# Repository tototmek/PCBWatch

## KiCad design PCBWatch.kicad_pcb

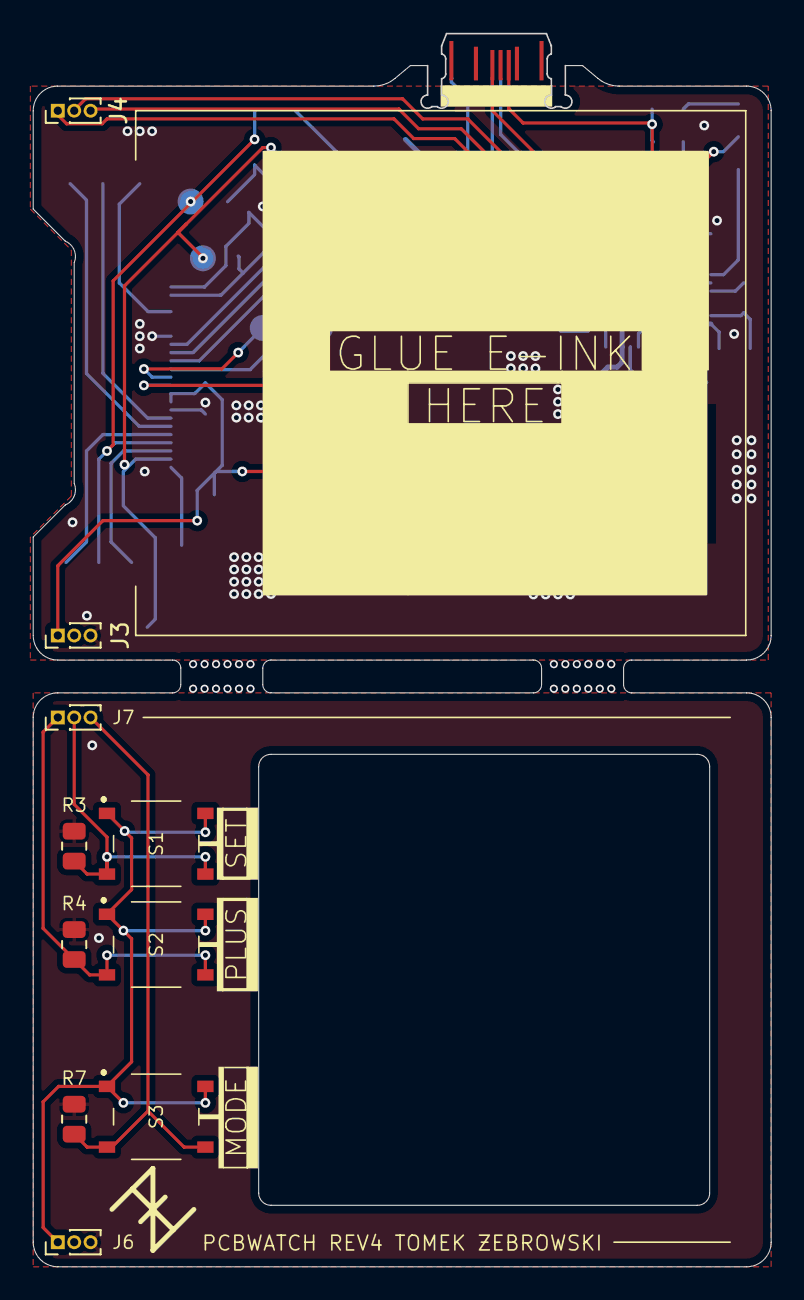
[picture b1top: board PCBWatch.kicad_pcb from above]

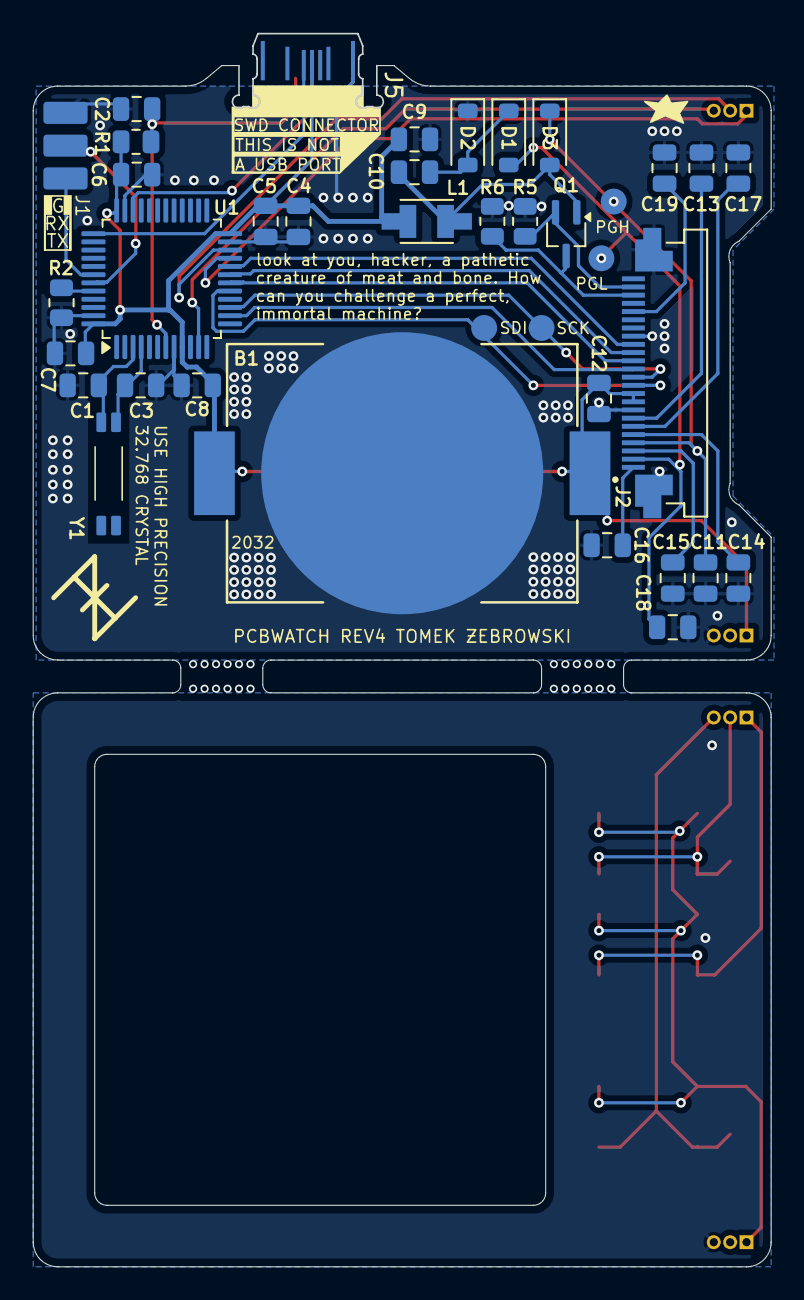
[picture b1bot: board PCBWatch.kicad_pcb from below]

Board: 2 copper layers, 44.9 x 75.2 mm, 45 parts (33 on the bottom side), 36 nets.

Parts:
B1: BAT-HLD-001; BATT_HLDR_LNX
C1, C3: 10p; C_0805_2012Metric
C2, C5, C6, C7, C8: 0.1u; C_0805_2012Metric
C4: 10u; C_0805_2012Metric
C9, C10: 4u7; C_0805_2012Metric
C11, C12, C13, C14, C15, C16, C18, C19: 1u; C_0805_2012Metric
C17: 1u(optional); C_0805_2012Metric
D1, D2, D3: MBR0530; D_SOD-123
J1: UART Pads; Untitled_2
J2: E-Ink connector; AMPHENOL_SFV24R-1STE1HLF
J3: Pin header A; PinHeader_1x03_P1.00mm_Vertical
J4: Pin header B; PinHeader_1x03_P1.00mm_Vertical
J5: PCBTypeC_14P
J6: Pin header A top; PinHeader_1x03_P1.00mm_Vertical
J7: Pin header B top; PinHeader_1x03_P1.00mm_Vertical
L1: 10u/47u; IND_LQH32CN100K23L
Q1: Si1304BDL / Si1308EDL TUBE MOS; SOT-323_SC-70_Handsoldering
R1, R2: 10K; R_0805_2012Metric
R3, R4, R7: 100K; R_0805_2012Metric
R5: 10k; R_0805_2012Metric
R6: 3/0.47/2.2; R_0805_2012Metric
S1, S2, S3: BUTTON; PTS526SM15SMTR2LFS
U1: STM32L010C6Tx; LQFP-48_7x7mm_P0.5mm
Y1: 32.768KHZ; XTAL_AB26T-32.768KHZ
e-ink1: E-Ink 1.54 Display

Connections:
+3V0: B1.1, C4.1, C5.1, C6.1, C7.1, C8.1, C9.1, C12.1, J2.15 (VDDIO), J2.16 (VCI), J3.1, J5.B6 (DP2), L1.1, R1.2, U1.9 (VDDA), U1.24 (VDD), U1.36 (VDD), U1.48 (VDD)
+3V0-T: J6.1, S1.1, S1.2, S2.1, S2.2, S3.1, S3.2
/BUSY: J2.9 (BUSY), U1.20 (PB2)
/BUTTON1: J4.2, U1.22 (PB11)
/BUTTON1-T: J7.2, R3.1, S1.3, S1.4
/BUTTON2: J4.1, U1.21 (PB10)
/BUTTON2-T: J7.1, R4.1, S2.3, S2.4
/BUTTON3: J4.3, U1.11 (PA1)
/BUTTON3-T: J7.3, R7.1, S3.3, S3.4
/CS: J2.12 (CS), U1.14 (PA4)
/D/C: J2.11 (D/C), U1.18 (PB0)
/GDR: J2.2 (GDR), Q1.2 (G), R5.2
/NRST: C2.1, J5.A5 (CC1), R1.1, U1.7 (NRST)
/PREVGH: C11.1, D3.1 (K), J2.21 (PREVGH)
/PREVGL: C18.1, D1.2 (A), J2.23 (PREVGL)
/RES: J2.10 (RES), U1.19 (PB1)
/RESE: J2.3 (RESE), Q1.3 (S), R6.2
/RX: J1.2, U1.43 (PB7)
/SCLK: J2.13 (SCL), U1.15 (PA5)
/SDI: J2.14 (SDA), U1.17 (PA7)
/SWCLK: J5.B7 (DN2), U1.37 (PA14)
/SWDIO: J5.A7 (DN1), U1.34 (PA13)
/TX: J1.1, U1.42 (PB6)
GND: B1.2, C1.2, C2.2, C3.2, C4.2, C5.2, C6.2, C7.2, C8.2, C9.2, C11.2, C12.2, C13.2, C14.2, C15.2, C16.2, C17.2, C18.2, C19.2, D2.1 (K), J1.3, J2.8 (BS), J2.17 (VSS), J2.SH1, J2.SH2, J3.3, J5.B1 (GND), R2.1, R5.1, R6.1, U1.8 (VSSA), U1.23 (VSS), U1.35 (VSS), U1.47 (VSS)
GND-T: J6.3, R3.2, R4.2, R7.2
unnamed: C10.1, D1.1 (K), D2.2 (A)
unnamed: C10.2, D3.2 (A), L1.2, Q1.1 (D)
unnamed: C16.1, J2.24 (VCOM)
unnamed: C13.1, J2.18 (VDD)
unnamed: C17.1, J2.19 (VPP)
unnamed: C14.1, J2.20 (VSH1)
unnamed: C19.1, J2.5 (VSH2)
unnamed: C15.1, J2.22 (VSL)
unnamed: R2.2, U1.44 (BOOT0)
unnamed: C1.1, U1.3 (PC14), Y1.1
unnamed: C3.1, U1.4 (PC15), Y1.4

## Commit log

2025-07-13 Initial commit, v2
2025-07-13 Two level board
2025-11-15 Push old changes of version 3
2025-11-16 E-ink first idea
2025-11-16 Semi-finished rev4 pcb
2025-11-17 Fix fpc pin ordering
2025-11-19 Add prevgh prevgl testpoints
2025-11-20 Finalize PCB for manufacturing
2025-12-16 Fix label error
